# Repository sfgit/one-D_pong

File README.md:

# One D Pong
One dimensional pong board &amp; source code (made using Autodesk EAGLE 9.2)

This handheld version of One D pong was inspired by One D pong that a friend built for a Hackaday event ages ago.  The source code here (new) supports both one-player and two-player versions.  The files were designed in EAGLE.  To get the firmware programmed:

1)  Plug in your OTS Arduino Uno and setup as a programmer by loading the Arduino as ISP project and programming it.
2)  Next up, install a library to support programming ATMEGA 328P (there are MANY)...A few I use are:
    - https://github.com/leomil72/megax8
    - https://forum.arduino.cc/index.php?topic=412070
    
    FWIW, that second option is magical.  It uses Optiboot and is super user-friendly.  Follow the instructions on their    website and you can't go wrong.

3) Once you have that package installed, you can select the ATMEGA328 as the target and connect the Arduino's SPI (ISP) connections to the board's right-angle programming header...The pins are called out in the silkscreen on the board.
4) You'll first need to load the Arduino bootloader and you do this from the Arduino IDE using Tools->Burn Bootloader
5) With the bootloader flashed, you can then program any arduino sketch onto the board though since this is purpose-built for One-D pong, I would of course suggest using the One-D pong .ino file in this repo.

A few things to note:

- The LED driver ICs can sink more than they source.  They can only source about 10mA but they can sink something like 25mA.  This is why the LED cathodes are wired into those driver ICs and not to GND.  
- These boards were designed to be hand assembled and since I'm profoundly lazy, I chose to use Resistor Arrays and not individual resistors.  These little devices are small but they can definitely be hand soldered, probably far more easily than the TSSOP packages that the LED drivers use.  
- I made my own stencils using Kapton using the Glowforge Pro.  You can cut 5mil Dupont Kapton (non-adhesive) which you can get from Amazon using the following settings:
  - Speed: 650
  - Power: 90%
  - Passes: 3
  - Lines Per Inch: 225
  - Focus Height: 0.005in.

  This worked like a charm but took some cleanup afterwards.  The benefit of a stencil is of course repeatability.  If you have difficulty cutting Kapton, buy Mylar in 4mil sheets (again, Amazon) and cut that. 4mil Mylar will also take several passes to cut thru but I used settings very similar to the Kapton and that worked good.

Working version:

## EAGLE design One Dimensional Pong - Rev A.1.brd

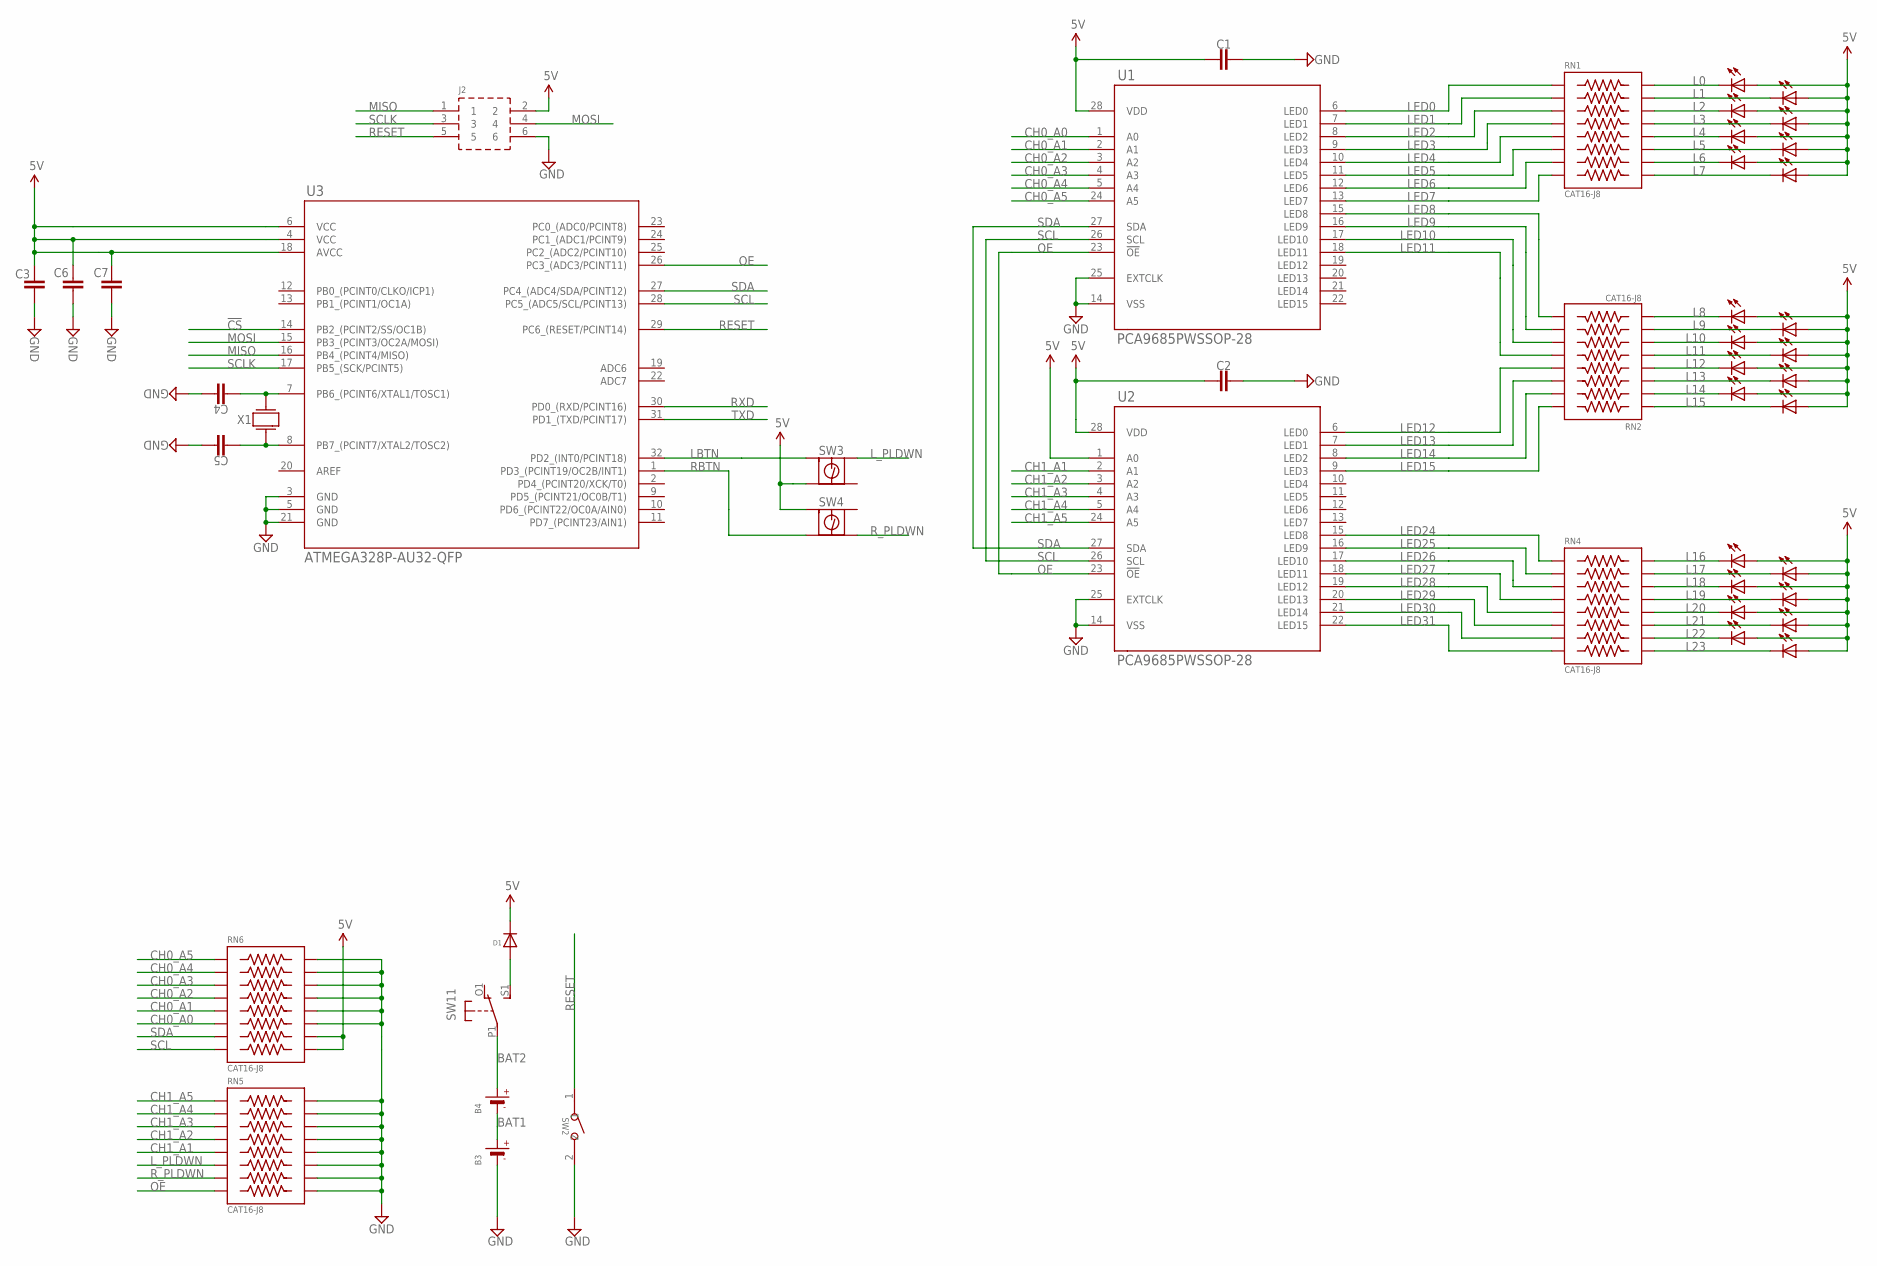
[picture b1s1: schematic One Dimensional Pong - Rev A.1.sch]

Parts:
B3, B4: BATTERYCR2540-SMT; CR2450
C1, C2, C3, C4, C5, C6, C7: C-EUC0805; C0805
D1: 1N4150W; SOD-123
J2: 610106249121; RA-SMT-HDR-2X3
LED1, LED5, LED28, LED32: LED0805-YELLOW; CHIP-LED0805-YELLOW
LED2, LED4, LED29, LED31: LED0805-ORANGE; CHIP-LED0805-ORANGE
LED3, LED30: LEDCHIPLED_0805; CHIPLED_0805
LED6, LED7, LED8, LED9, LED10, LED11, LED12, LED13, LED14, LED15, LED16, LED25, LED26, LED27: LED0805-GREEN; CHIP-LED0805-GREEN
RN1, RN2, RN4, RN5, RN6: CAT16-J8; RN8
SW1: DPDT-EG1390; EG1390
SW2: B3U-1000P-2P-SMD; SW2-2.6-3.0X2.5X1.2+0.4MM
SW3, SW4: PTS645SM43SMTR92LFS; PTS645-SMT-6MM
U1, U2: PCA9685PWSSOP-28; SOP65P640X110-28
U3: ATMEGA328P-AU32-QFP; QFP80P897X897X120-32
X1: ABLS-16.000MHZ-B4-T; OSC12P7X4P7

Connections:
5V: C1.1, C2.1, C3.1, C6.1, C7.1, D1.K (C), J2.2, LED1.A, LED2.A, LED3.A, LED4.A, LED5.A, LED6.A, LED7.A, LED8.A, LED9.A, LED10.A, LED11.A, LED12.A, LED13.A, LED14.A, LED15.A, LED16.A, LED25.A, LED26.A, LED27.A, LED28.A, LED29.A, LED30.A, LED31.A, LED32.A, RN6.14, RN6.16, SW3.P$3 (3), SW4.P$1 (1), U1.28 (VDD), U2.1 (A0), U2.28 (VDD), U3.4 (VCC), U3.6 (VCC), U3.18 (AVCC)
!CS: U3.14 (PB2_(PCINT2/SS/OC1B))
BAT1: B3.1 (+), B3.2 (+), B4.GND (-)
BAT2: B4.1 (+), B4.2 (+), SW1.P1
CH0_A0: RN6.11, U1.1 (A0)
CH0_A1: RN6.9, U1.2 (A1)
CH0_A2: RN6.7, U1.3 (A2)
CH0_A3: RN6.5, U1.4 (A3)
CH0_A4: RN6.3, U1.5 (A4)
CH0_A5: RN6.1, U1.24 (A5)
CH1_A1: RN5.9, U2.2 (A1)
CH1_A2: RN5.7, U2.3 (A2)
CH1_A3: RN5.5, U2.4 (A3)
CH1_A4: RN5.3, U2.5 (A4)
CH1_A5: RN5.1, U2.24 (A5)
GND: B3.GND (-), C1.2, C2.2, C3.2, C4.2, C5.2, C6.2, C7.2, J2.6, RN5.2, RN5.4, RN5.6, RN5.8, RN5.10, RN5.12, RN5.14, RN5.16, RN6.2, RN6.4, RN6.6, RN6.8, RN6.10, RN6.12, SW2.2, U1.14 (VSS), U1.25 (EXTCLK), U2.14 (VSS), U2.25 (EXTCLK), U3.3 (GND), U3.5 (GND), U3.21 (GND)
L0: LED1.C, RN1.2
L1: LED2.C, RN1.4
L2: LED3.C, RN1.6
L3: LED4.C, RN1.8
L4: LED5.C, RN1.10
L5: LED6.C, RN1.12
L6: LED7.C, RN1.14
L7: LED8.C, RN1.16
L8: LED9.C, RN2.15
L9: LED10.C, RN2.13
L10: LED11.C, RN2.11
L11: LED12.C, RN2.9
L12: LED13.C, RN2.7
L13: LED14.C, RN2.5
L14: LED15.C, RN2.3
L15: LED16.C, RN2.1
L16: LED25.C, RN4.2
L17: LED26.C, RN4.4
L18: LED27.C, RN4.6
L19: LED28.C, RN4.8
L20: LED29.C, RN4.10
L21: LED30.C, RN4.12
L22: LED31.C, RN4.14
L23: LED32.C, RN4.16
LBTN: SW3.P$1 (1), U3.32 (PD2_(INT0/PCINT18))
LED0: RN1.1, U1.6 (LED0)
LED1: RN1.3, U1.7 (LED1)
LED2: RN1.5, U1.8 (LED2)
LED3: RN1.7, U1.9 (LED3)
LED4: RN1.9, U1.10 (LED4)
LED5: RN1.11, U1.11 (LED5)
LED6: RN1.13, U1.12 (LED6)
LED7: RN1.15, U1.13 (LED7)
LED8: RN2.16, U1.15 (LED8)
LED9: RN2.14, U1.16 (LED9)
LED10: RN2.12, U1.17 (LED10)
LED11: RN2.10, U1.18 (LED11)
LED12: RN2.8, U2.6 (LED0)
LED13: RN2.6, U2.7 (LED1)
LED14: RN2.4, U2.8 (LED2)
LED15: RN2.2, U2.9 (LED3)
LED24: RN4.1, U2.15 (LED8)
LED25: RN4.3, U2.16 (LED9)
LED26: RN4.5, U2.17 (LED10)
LED27: RN4.7, U2.18 (LED11)
LED28: RN4.9, U2.19 (LED12)
LED29: RN4.11, U2.20 (LED13)
LED30: RN4.13, U2.21 (LED14)
LED31: RN4.15, U2.22 (LED15)
L_PLDWN: RN5.11, SW3.P$2 (2)
MISO: J2.1, U3.16 (PB4_(PCINT4/MISO))
MOSI: J2.4, U3.15 (PB3_(PCINT3/OC2A/MOSI))
unnamed: C4.1, U3.7 (PB6_(PCINT6/XTAL1/TOSC1)), X1.2
unnamed: C5.1, U3.8 (PB7_(PCINT7/XTAL2/TOSC2)), X1.1
unnamed: D1.A, SW1.S1 (S)
OE: RN5.15, U1.23 (!OE), U2.23 (!OE), U3.26 (PC3_(ADC3/PCINT11))
RBTN: SW4.P$3 (3), U3.1 (PD3_(PCINT19/OC2B/INT1))
RESET: J2.5, SW2.1, U3.29 (PC6_(RESET/PCINT14))
RXD: U3.30 (PD0_(RXD/PCINT16))
R_PLDWN: RN5.13, SW4.P$4 (4)
SCL: RN6.15, U1.26 (SCL), U2.26 (SCL), U3.28 (PC5_(ADC5/SCL/PCINT13))
SCLK: J2.3, U3.17 (PB5_(SCK/PCINT5))
SDA: RN6.13, U1.27 (SDA), U2.27 (SDA), U3.27 (PC4_(ADC4/SDA/PCINT12))
TXD: U3.31 (PD1_(TXD/PCINT17))

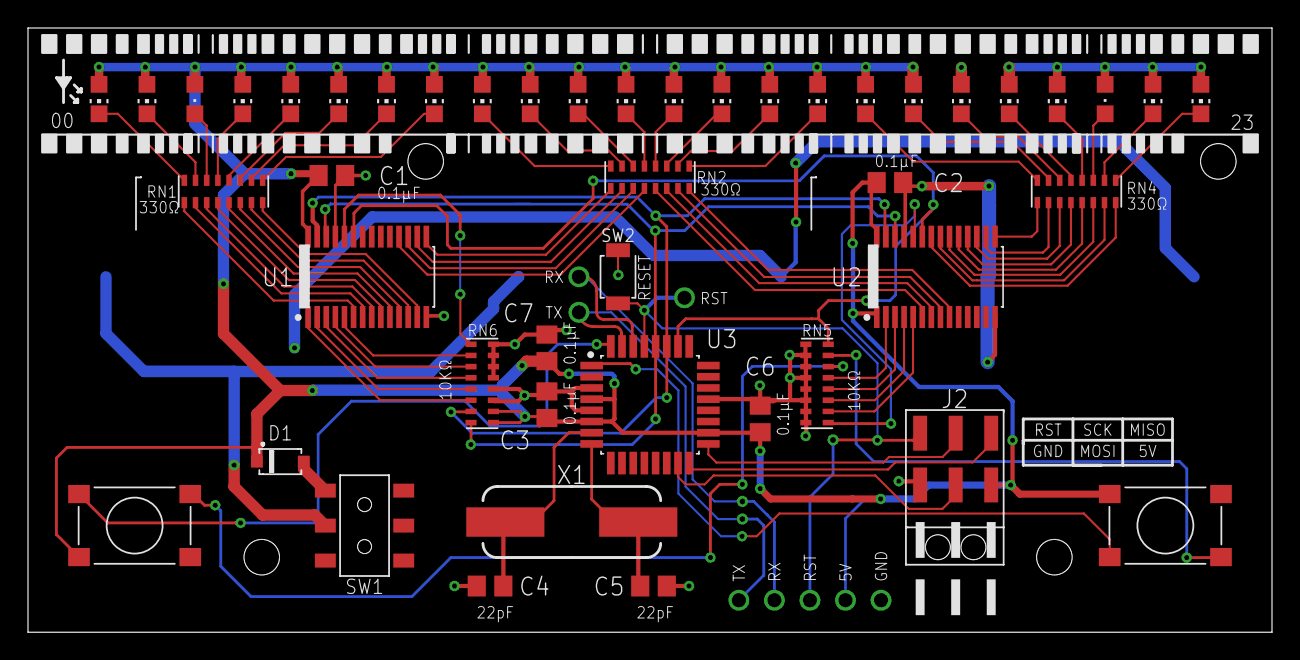
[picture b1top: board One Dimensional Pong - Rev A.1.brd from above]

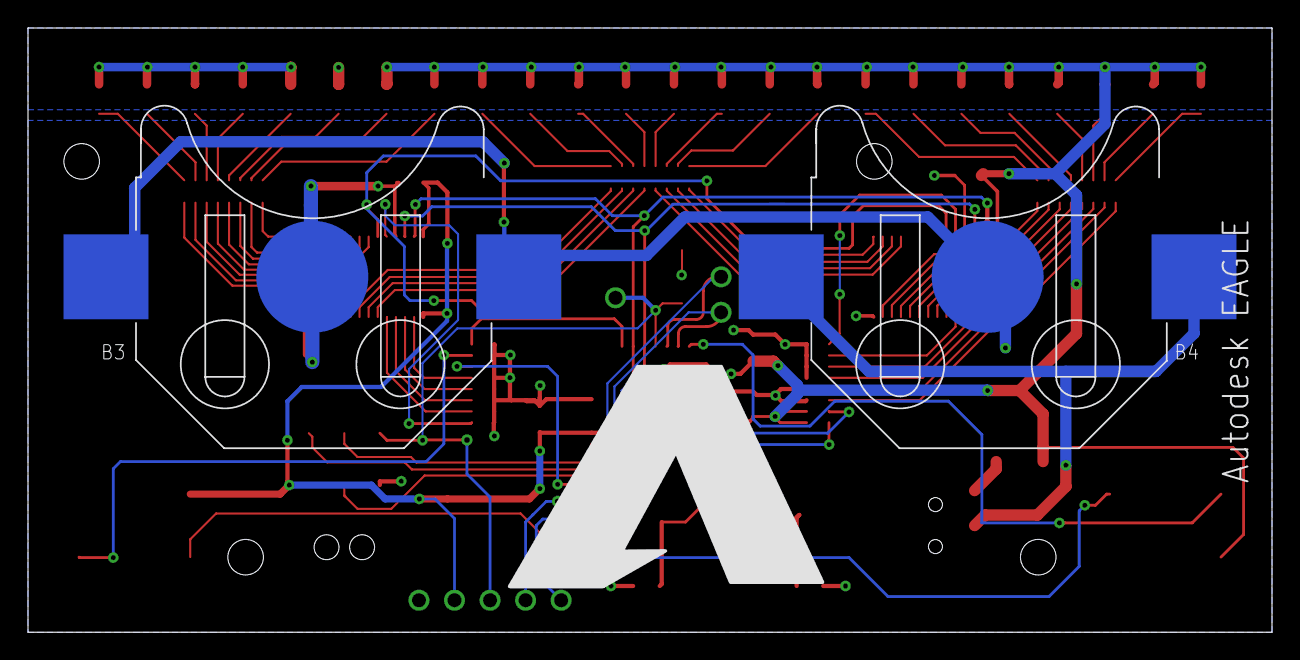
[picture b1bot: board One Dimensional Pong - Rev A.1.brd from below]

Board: 2 copper layers, 88.9 x 43.2 mm, 48 parts (2 on the bottom side), 77 nets.
